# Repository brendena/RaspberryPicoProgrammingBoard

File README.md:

# boards
## PicoProbeProgrammerBoard

A board to help with programming and debugging the raspberry pi pico.  I have a standard 2x5 pin connector that can carry swd, power and some extra debug signals

connectors 
* 1.27mm 2x5 Pin 10 Pin SMT
* 2.54mm 7 pin breakout jtag
* 3 1.0mm jst connector - used on the pico with that comes pre soldiered

## PicoDebugInterface

This is a small board that sites ontop of the main raspberry pi pico to add a 2x5 pin connector ontop to make it easier to program with the option to add extra debug pin as well.

# RaspberryPi_PicoProgrammer

This board will make programming the pico a little cleaner.  It shares most of the features that the PicoProbeProgrammerBoard has.  But with the added benifit have being able to directly read the i2c's or debug connections while directly from the pi.

* Potentially very usfull with a right angle for the pi 4000.  So you can easily add debugging ability to that board.

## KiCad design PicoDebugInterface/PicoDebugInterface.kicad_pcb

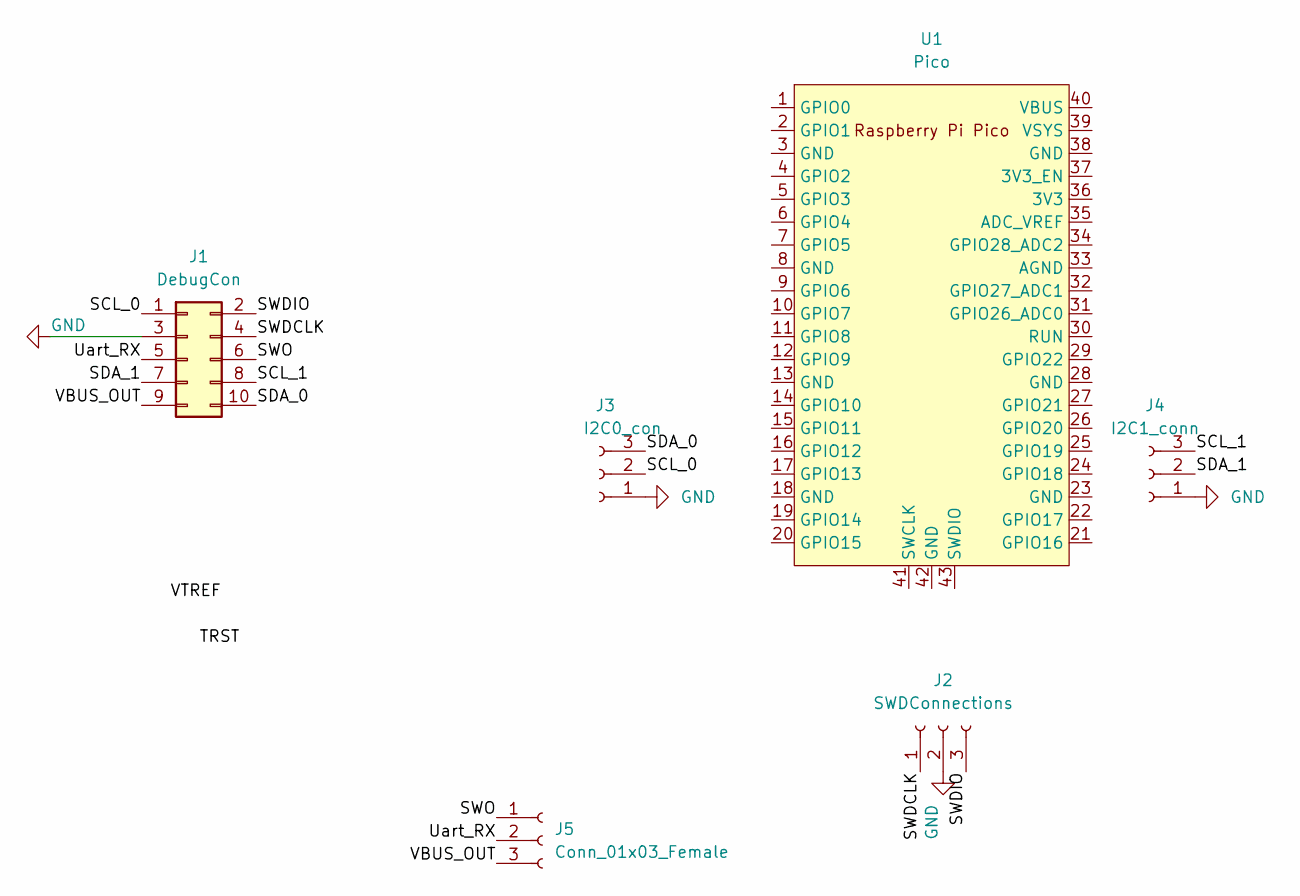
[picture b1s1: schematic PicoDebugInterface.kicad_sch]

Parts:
J1: DebugCon; 3220-10-0300-00-TR
J2: SWDConnections; BottomSWDConnection
J3: I2C0_con; BottomSWDConnection
J4: I2C1_conn; BottomSWDConnection
J5: Conn_01x03_Female; BottomSWDConnection
U1: Pico; RPi_Pico_SMD_TH

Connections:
/SCL_0: J1.1, J3.2
/SCL_1: J1.8, J4.3
/SDA_0: J1.10, J3.3
/SDA_1: J1.7, J4.2
/SWDCLK: J1.4, J2.1
/SWDIO: J1.2, J2.3
/SWO: J1.6, J5.1
/Uart_RX: J1.5, J5.2
/VBUS_OUT: J1.9, J5.3
GND: J1.3, J2.2, J3.1, J4.1

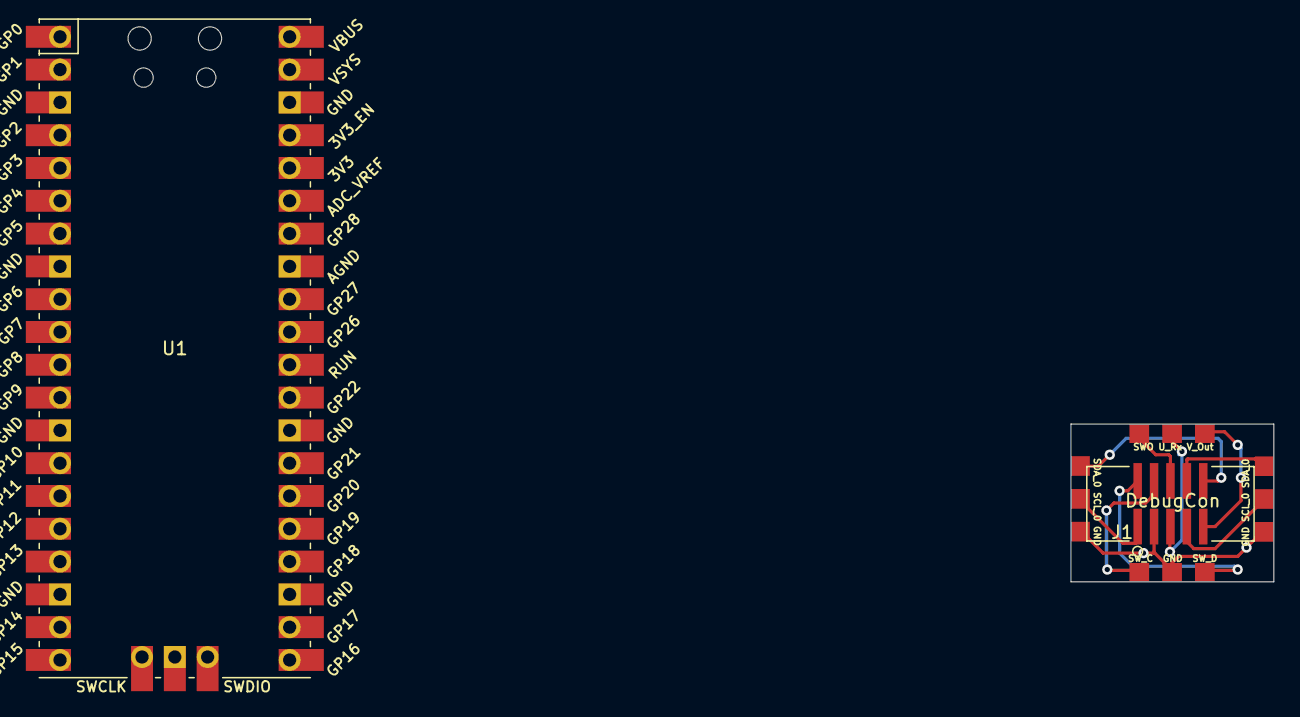
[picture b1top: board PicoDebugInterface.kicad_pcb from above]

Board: 2 copper layers, 15.7 x 12.2 mm, 6 parts (0 on the bottom side), 10 nets.

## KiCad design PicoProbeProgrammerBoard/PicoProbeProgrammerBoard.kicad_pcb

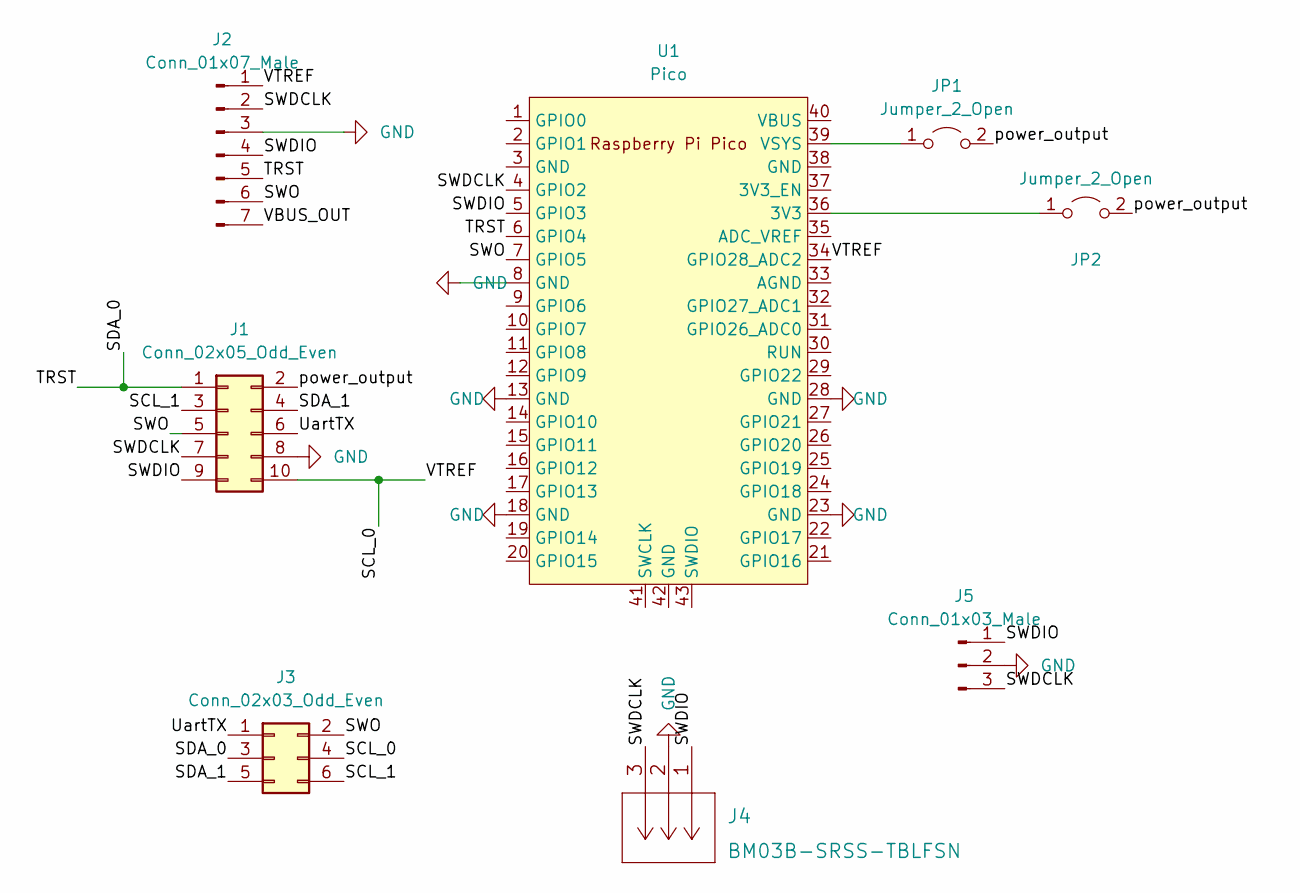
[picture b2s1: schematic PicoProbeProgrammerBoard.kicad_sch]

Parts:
J1: Conn_02x05_Odd_Even; 3220-10-0300-00-TR
J2: Conn_01x07_Male; PinSocket_1x07_P2.54mm_Horizontal
J3: Conn_02x03_Odd_Even; PinSocket_2x03_P2.54mm_Vertical
J4: BM03B-SRSS-TBLFSN
J5: Conn_01x03_Male; PinSocket_1x03_P2.54mm_Vertical
JP1, JP2: Jumper_2_Open; PinHeader_1x02_P2.54mm_Vertical
U1: Pico; RPi_Pico_SMD_TH

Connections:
/SCL_0: J1.10, J2.1, J3.4, U1.34 (GPIO28_ADC2)
/SCL_1: J1.3, J3.6
/SDA_0: J1.1, J2.5, J3.3, U1.6 (GPIO4)
/SDA_1: J1.4, J3.5
/SWDCLK: J1.7, J2.2, J4.3, J5.3, U1.4 (GPIO2)
/SWDIO: J1.9, J2.4, J4.1, J5.1, U1.5 (GPIO3)
/SWO: J1.5, J2.6, J3.2, U1.7 (GPIO5)
/UartTX: J1.6, J3.1
/VBUS_OUT: J2.7
/power_output: J1.2, JP1.2 (B), JP2.2 (B)
GND: J1.8, J2.3, J4.2, J5.2, U1.8 (GND), U1.13 (GND), U1.18 (GND), U1.23 (GND), U1.28 (GND)
unnamed: JP1.1 (A), U1.39 (VSYS)
unnamed: JP2.1 (A), U1.36 (3V3)

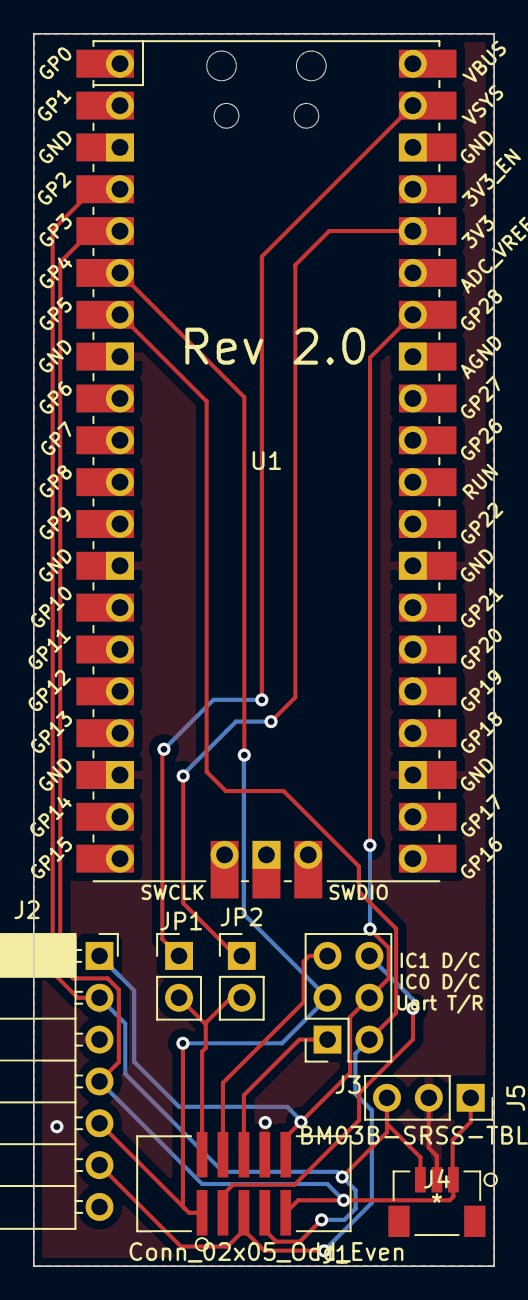
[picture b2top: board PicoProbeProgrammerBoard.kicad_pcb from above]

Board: 2 copper layers, 27.9 x 74.8 mm, 8 parts (0 on the bottom side), 12 nets.

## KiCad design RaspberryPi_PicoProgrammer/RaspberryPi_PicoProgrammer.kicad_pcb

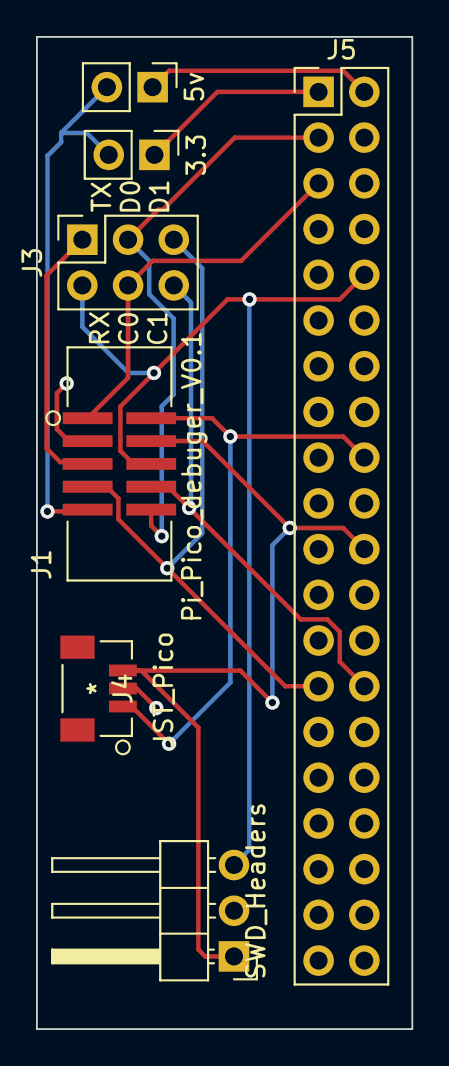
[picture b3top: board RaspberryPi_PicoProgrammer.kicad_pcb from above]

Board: 2 copper layers, 20.9 x 55.1 mm, 7 parts (0 on the bottom side), 12 nets.

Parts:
3.3, 5v: Jumper_2_Open; PinHeader_1x02_P2.54mm_Vertical
J1: Pi_Pico_debuger_V0.1; 3220-10-0300-00-TR
J3: Conn_Extra; PinSocket_2x03_P2.54mm_Vertical
J4: JST_Pico; BM03B-SRSS-TBLFSN
J5: Raspberry_Pi_2_3; PinHeader_2x20_P2.54mm_Vertical
SWD_Headers: Conn_01x03_Male; PinHeader_1x03_P2.54mm_Horizontal

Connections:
/SCL_0: J1.1, J3.4, J5.5 (SCL/GPIO3)
/SCL_1: J1.8, J3.6, J5.28 (ID_SC/GPIO1)
/SDA_0: J1.10, J3.3, J5.3 (SDA/GPIO2)
/SDA_1: J1.7, J3.5, J5.27 (ID_SD/GPIO0)
/SWDCLK: J1.4, J4.3, J5.22 (GPIO25), SWD_Headers.1
/SWDIO: J1.2, J4.1, J5.18 (GPIO24)
/SWO: J1.6, J3.2, J5.10 (GPIO15/RXD), SWD_Headers.3
/UartTX: J1.5, J3.1, J5.8 (GPIO14/TXD)
/power_output: 3.3.2 (B), 5v.2 (B), J1.9
GND: J1.3, J4.2, J5.6 (GND), J5.9 (GND), J5.14 (GND), J5.20 (GND), J5.25 (GND), J5.30 (GND), J5.34 (GND), J5.39 (GND), SWD_Headers.2
unnamed: 3.3.1 (A), J5.1 (3V3)
unnamed: 5v.1 (A), J5.2 (5V)

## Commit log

2022-09-28 added the ignore docs
2022-09-28 added boards
2022-09-28 removed modules
2022-09-28 added the actuall boards
2022-09-28 added layout
2022-09-29 added schematic for raspberry pi
2022-09-29 removed garabage
2022-10-02 almost done the board layout
2022-10-03 board sent out
2022-10-19 stuff submitted for 1 ref
2022-10-21 pushed fix for the connector so it a staight through cable

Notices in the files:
parts and their libraries:
Copyright 2021 Accelerated Designs. All rights reserved.
